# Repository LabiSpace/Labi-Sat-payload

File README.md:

# Labi-Sat-payload

KiCad 10 design for a sample payload board for the Labi Sat PocketQube platform. The
schematic includes two RP2040 MCU boards and the `PQ_bus` interface.

## Schematic notes

- GP18 is available for use, but is also internally connected to an LED.
- Unassigned GPIOs can be used for any function.
- If the HDUART interface is used, do not connect anything else to GPIO0 / GPIO4.
- Net names may be changed as needed, but **do not connect**
  `REG_BUS_PROTECTED_1` and `REG_BUS_PROTECTED_2` together.

## PQ_bus pinout

2×8, 2.54 mm card-edge connector (`pq:PinHeader_2x8_2.54_PCB_edge`).

| Pin | Signal              | Pin | Signal              |
|-----|---------------------|-----|---------------------|
| 1   | GND                 | 2   | DNC                 |
| 3   | DNC                 | 4   | HDUART_2            |
| 5   | DNC                 | 6   | CAN2_H              |
| 7   | REG_BUS_PROTECTED_1 | 8   | CAN2_L              |
| 9   | CAN1_L              | 10  | REG_BUS_PROTECTED_2 |
| 11  | CAN1_H              | 12  | DNC                 |
| 13  | HDUART_1            | 14  | DNC                 |
| 15  | DNC                 | 16  | GND                 |

Pins marked DNC (do not connect) are reserved for future use and must be left
unconnected on the payload board. The board is powered from the bus, so the
supply pins of the `PQ_bus` symbol are power outputs and no `PWR_FLAG` is needed.

## Design files

- `payoad_board.kicad_sch` — schematic
- `payoad_board.kicad_pcb` — PCB layout
- `payoad_board.kicad_pro` — KiCad project settings
- `pq.kicad_sym` — project symbol library (`MCU_1`, `PQ_bus`)
- `pq.pretty/` — project footprint library
- `3dmodels/` — 3D models used by the footprints
- `sym-lib-table`, `fp-lib-table` — project library tables (paths relative to `${KIPRJMOD}`)

Open `payoad_board.kicad_pro` in KiCad to view the project. All libraries and 3D models
are part of the repository, so no extra library setup is needed.

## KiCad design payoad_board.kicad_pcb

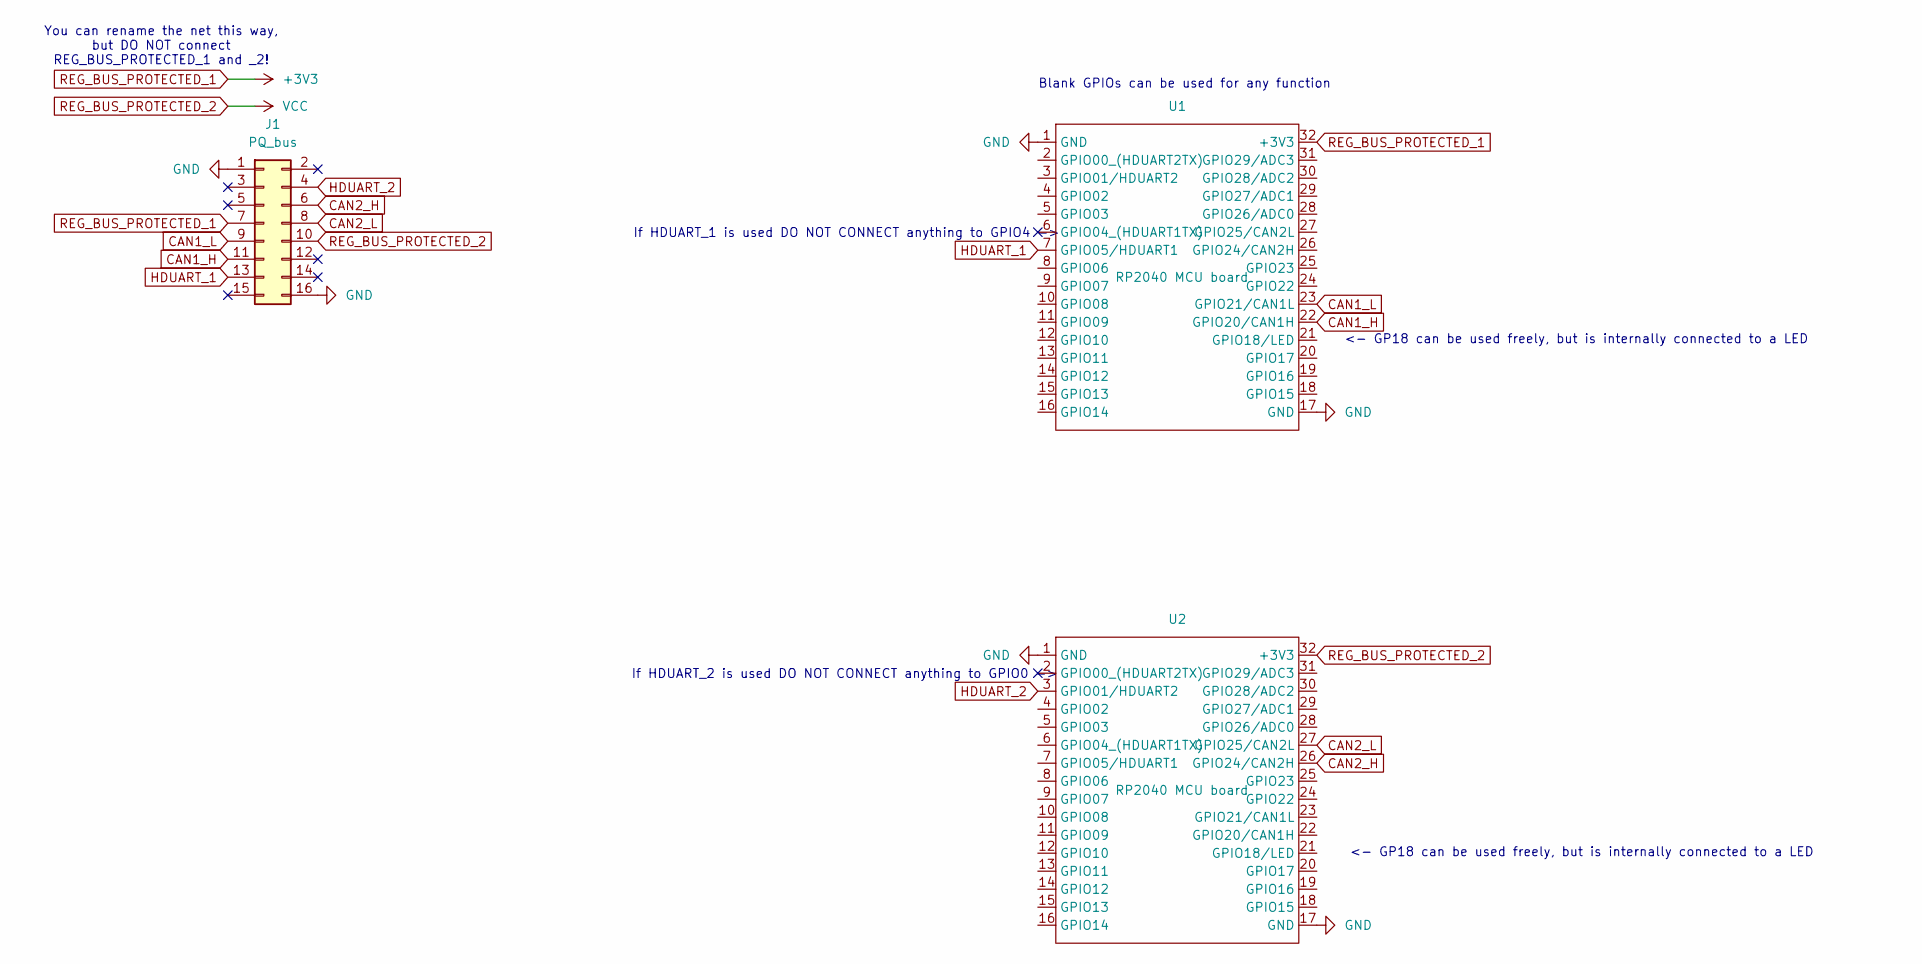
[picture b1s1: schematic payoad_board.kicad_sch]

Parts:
J1: PQ_bus; PinHeader_2x8_2.54_PCB_edge
U1, U2: RP2040 MCU board; MCU_board_127

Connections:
CAN1_H: J1.11 (CAN1_H), U1.22 (GPIO20/CAN1H)
CAN1_L: J1.9 (CAN1_L), U1.23 (GPIO21/CAN1L)
CAN2_H: J1.6 (CAN2_H), U2.26 (GPIO24/CAN2H)
CAN2_L: J1.8 (CAN2_L), U2.27 (GPIO25/CAN2L)
GND: J1.1 (GND), J1.16 (GND), U1.1 (GND), U1.17 (GND), U2.1 (GND), U2.17 (GND)
HDUART_1: J1.13 (HDUART_1), U1.7 (GPIO05/HDUART1)
HDUART_2: J1.4 (HDUART_2), U2.3 (GPIO01/HDUART2)
REG_BUS_PROTECTED_1: J1.7 (REG_BUS_PROTECTED_1), U1.32 (+3V3)
REG_BUS_PROTECTED_2: J1.10 (REG_BUS_PROTECTED_2), U2.32 (+3V3)

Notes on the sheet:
<- GP18 can be used freely, but is internally connected to a LED
You can rename the net this way, but DO NOT connect REG_BUS_PROTECTED_1 and _2!
If HDUART_2 is used DO NOT CONNECT anything to GPIO0 ->
If HDUART_1 is used DO NOT CONNECT anything to GPIO4 ->
Blank GPIOs can be used for any function

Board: 2 copper layers, 3 parts (1 on the bottom side), 9 nets, no tracks yet.

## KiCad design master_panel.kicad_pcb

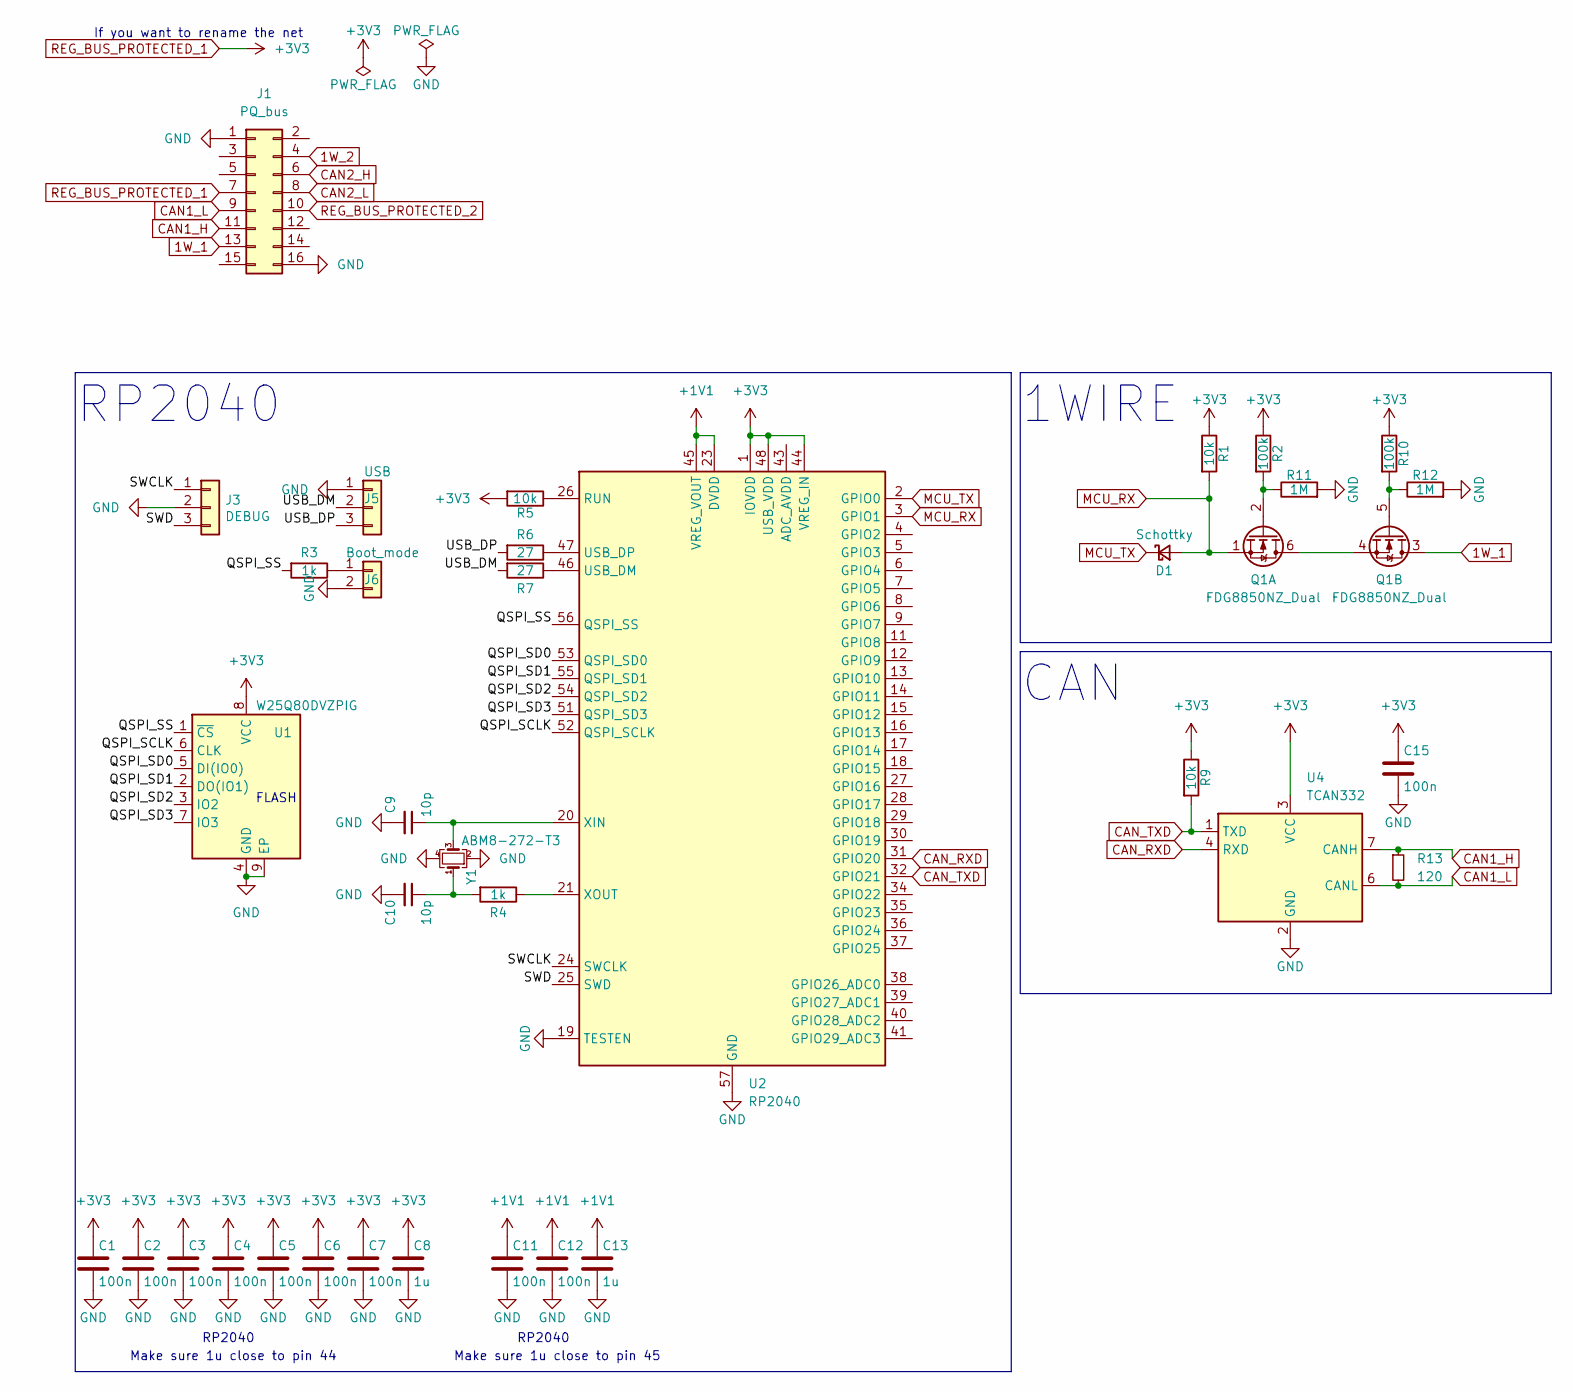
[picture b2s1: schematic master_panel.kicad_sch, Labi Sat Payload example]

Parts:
C1, C2, C3, C4, C5, C6, C7, C11, C12, C15: 100n; C_0402_1005Metric
C8, C13: 1u; C_0402_1005Metric
C9, C10: 10p; C_0402_1005Metric
D1: Schottky; D_SOD-323
J1: PQ_bus; PinHeader_2x8_2.54_PCB_edge
J3: DEBUG; PinHeader_1x03_P1.27mm_Vertical
J5: USB; PinHeader_1x03_P1.27mm_Vertical
J6: Boot_mode; PinHeader_1x02_P1.27mm_Vertical
Q1: FDG8850NZ_Dual; SOT65P210X110-6N
R1, R5, R9: 10k; R_0402_1005Metric
R2, R10: 100k; R_0402_1005Metric
R3, R4: 1k; R_0402_1005Metric
R6, R7: 27; R_0402_1005Metric
R11, R12: 1M; R_0402_1005Metric
R13: 120; R_0402_1005Metric
U1: W25Q80DVZPIG; SON127P600X500X80-9N-D_th
U2: RP2040; RP2040-QFN-56
U4: TCAN332; SOT-23-8
Y1: ABM8-272-T3; ABM8-12.000MHZ

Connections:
1W_1: J1.13, Q1.3 (D)
1W_2: J1.4
+1V1: C11.1, C12.1, C13.1, U2.23 (DVDD), U2.45 (VREG_VOUT), U2.50 (DVDD)
/QSPI_SCLK: U1.6 (CLK), U2.52 (QSPI_SCLK)
/QSPI_SD0: U1.5 (DI(IO0)), U2.53 (QSPI_SD0)
/QSPI_SD1: U1.2 (DO(IO1)), U2.55 (QSPI_SD1)
/QSPI_SD2: U1.3 (IO2), U2.54 (QSPI_SD2)
/QSPI_SD3: U1.7 (IO3), U2.51 (QSPI_SD3)
/QSPI_SS: R3.2, U1.1 (~CS), U2.56 (QSPI_SS)
/SWCLK: J3.1, U2.24 (SWCLK)
/SWD: J3.3, U2.25 (SWD)
/USB_DM: J5.2, R7.2
/USB_DP: J5.3, R6.2
CAN1_H: J1.11, R13.1, U4.7 (CANH)
CAN1_L: J1.9, R13.2, U4.6 (CANL)
CAN2_H: J1.6
CAN2_L: J1.8
CAN_RXD: U2.31 (GPIO20), U4.4 (RXD)
CAN_TXD: R9.2, U2.32 (GPIO21), U4.1 (TXD)
GND: C1.2, C2.2, C3.2, C4.2, C5.2, C6.2, C7.2, C8.2, C9.2, C10.2, C11.2, C12.2, C13.2, C15.2, J1.1, J1.16, J3.2, J5.1, J6.2, R11.2, R12.2, U1.4 (GND), U1.9 (EP), U2.19 (TESTEN), U2.57 (GND), U4.2 (GND), Y1.2, Y1.4
MCU_RX: D1.2 (A), Q1.1 (S), R1.2, U2.3 (GPIO1)
MCU_TX: D1.1 (K), U2.2 (GPIO0)
unnamed: C10.1, R4.2, Y1.1
unnamed: J6.1, R3.1
unnamed: Q1.4 (S), Q1.6 (D)
unnamed: Q1.2 (G), R2.2, R11.1
unnamed: Q1.5 (G), R10.2, R12.1
unnamed: R5.1, U2.26 (RUN)
unnamed: R7.1, U2.46 (USB_DM)
unnamed: R6.1, U2.47 (USB_DP)
unnamed: C9.1, U2.20 (XIN), Y1.3
unnamed: R4.1, U2.21 (XOUT)
REG_BUS_PROTECTED_1: C1.1, C2.1, C3.1, C4.1, C5.1, C6.1, C7.1, C8.1, C15.1, J1.7, R1.1, R2.1, R5.2, R9.1, R10.1, U1.8 (VCC), U2.1 (IOVDD), U2.10 (IOVDD), U2.22 (IOVDD), U2.33 (IOVDD), U2.42 (IOVDD), U2.44 (VREG_IN), U2.48 (USB_VDD), U2.49 (IOVDD), U4.3 (VCC)
REG_BUS_PROTECTED_2: J1.10

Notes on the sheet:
RP2040
FLASH
If you want to rename the net
Make sure 1u close to pin 45
CAN
Make sure 1u close to pin 44
1WIRE

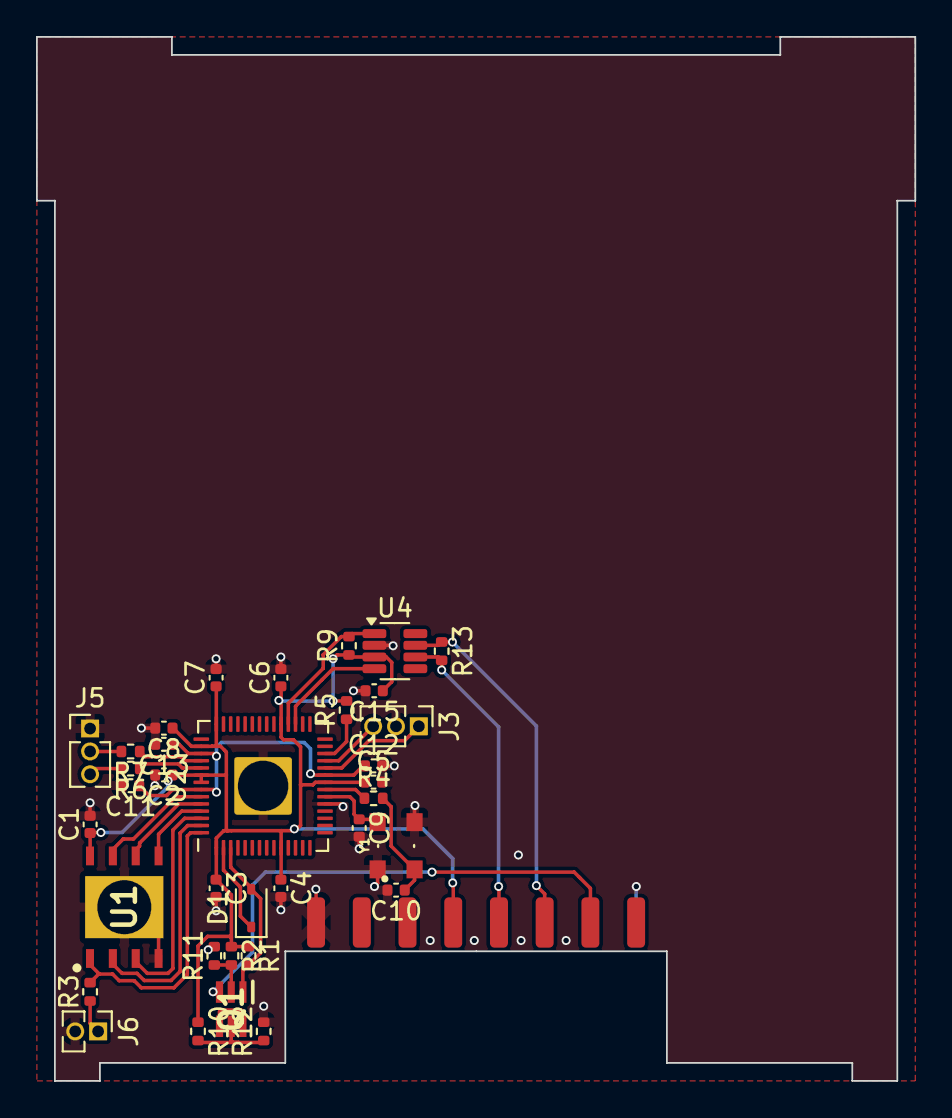
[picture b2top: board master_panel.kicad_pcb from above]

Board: 2 copper layers, 48.8 x 58.0 mm, 36 parts (0 on the bottom side), 30 nets.

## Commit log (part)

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2026-03-24 Initial commit
    Added first release of example payload hardware design.
